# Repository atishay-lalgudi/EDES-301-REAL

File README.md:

# EDES301
Repository for EDES 301 course work

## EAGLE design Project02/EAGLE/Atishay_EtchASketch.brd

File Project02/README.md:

# EDES 301 Project 2
Digital Etch-A-Sketch PCB is a custom two-layer printed circuit board designed in Autodesk EAGLE as part of the EDES301 course. The board interfaces a NUCLEO microcontroller development board with an Adafruit SPI LCD (Model 1770 or similar), providing analog input via two potentiometers for X/Y drawing control and digital input via two push buttons for functions such as clearing the screen or mode selection. Additional features include red, green, and blue status LEDs, a MicroSD card slot for saving or loading drawings, and dedicated headers for host board connectivity. The PCB follows standard manufacturing constraints, using 10 mil signal and 15 mil power traces, 12 mil drill / 24 mil diameter vias, and Gerber RS-274X files prepared for standard CAM fabrication.

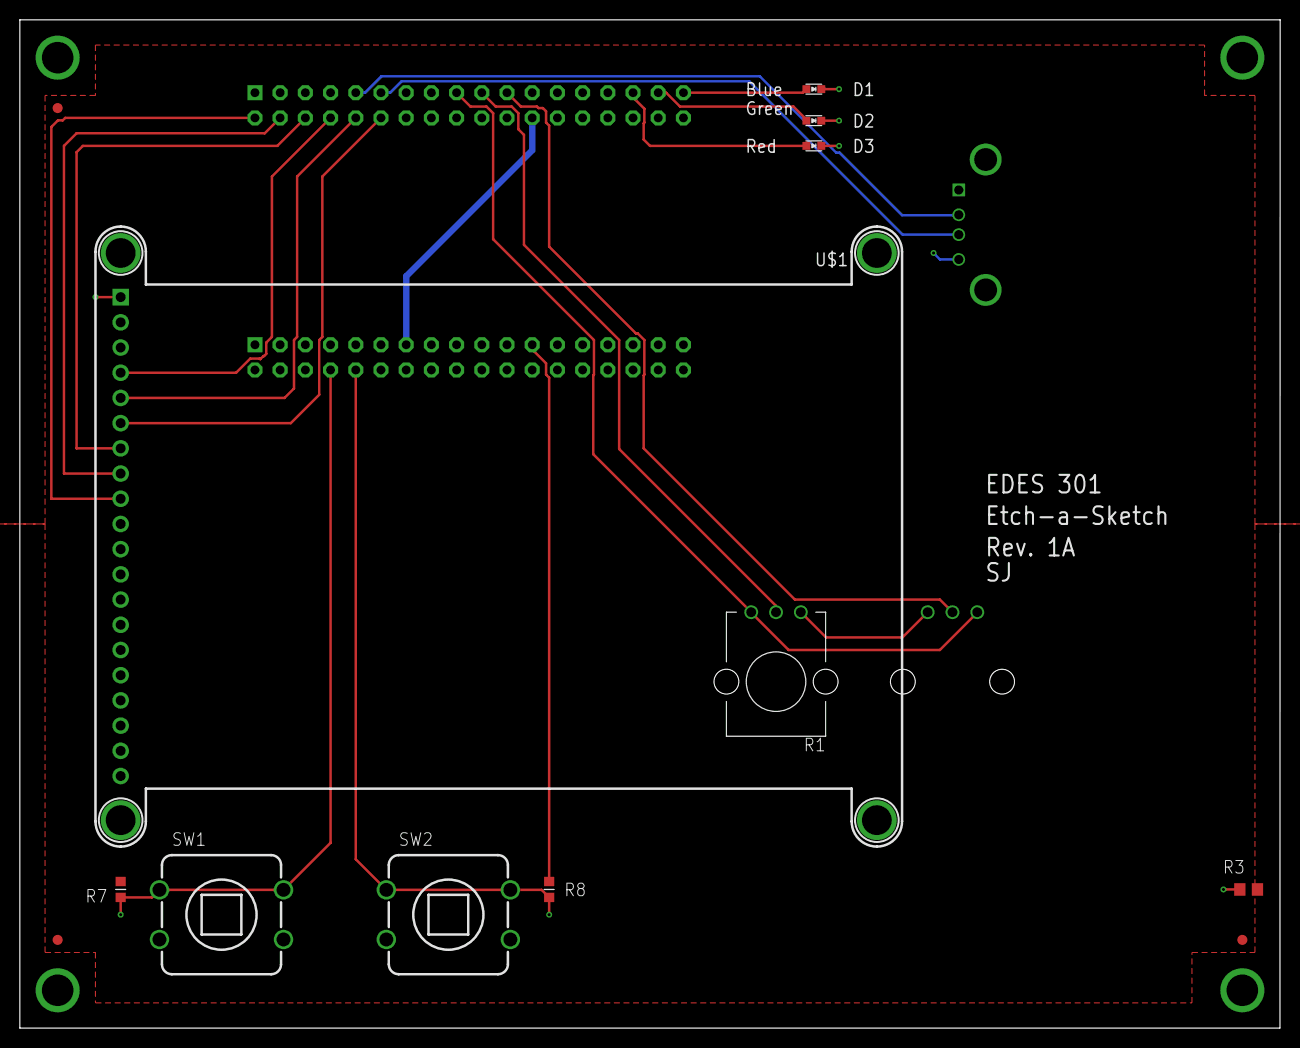
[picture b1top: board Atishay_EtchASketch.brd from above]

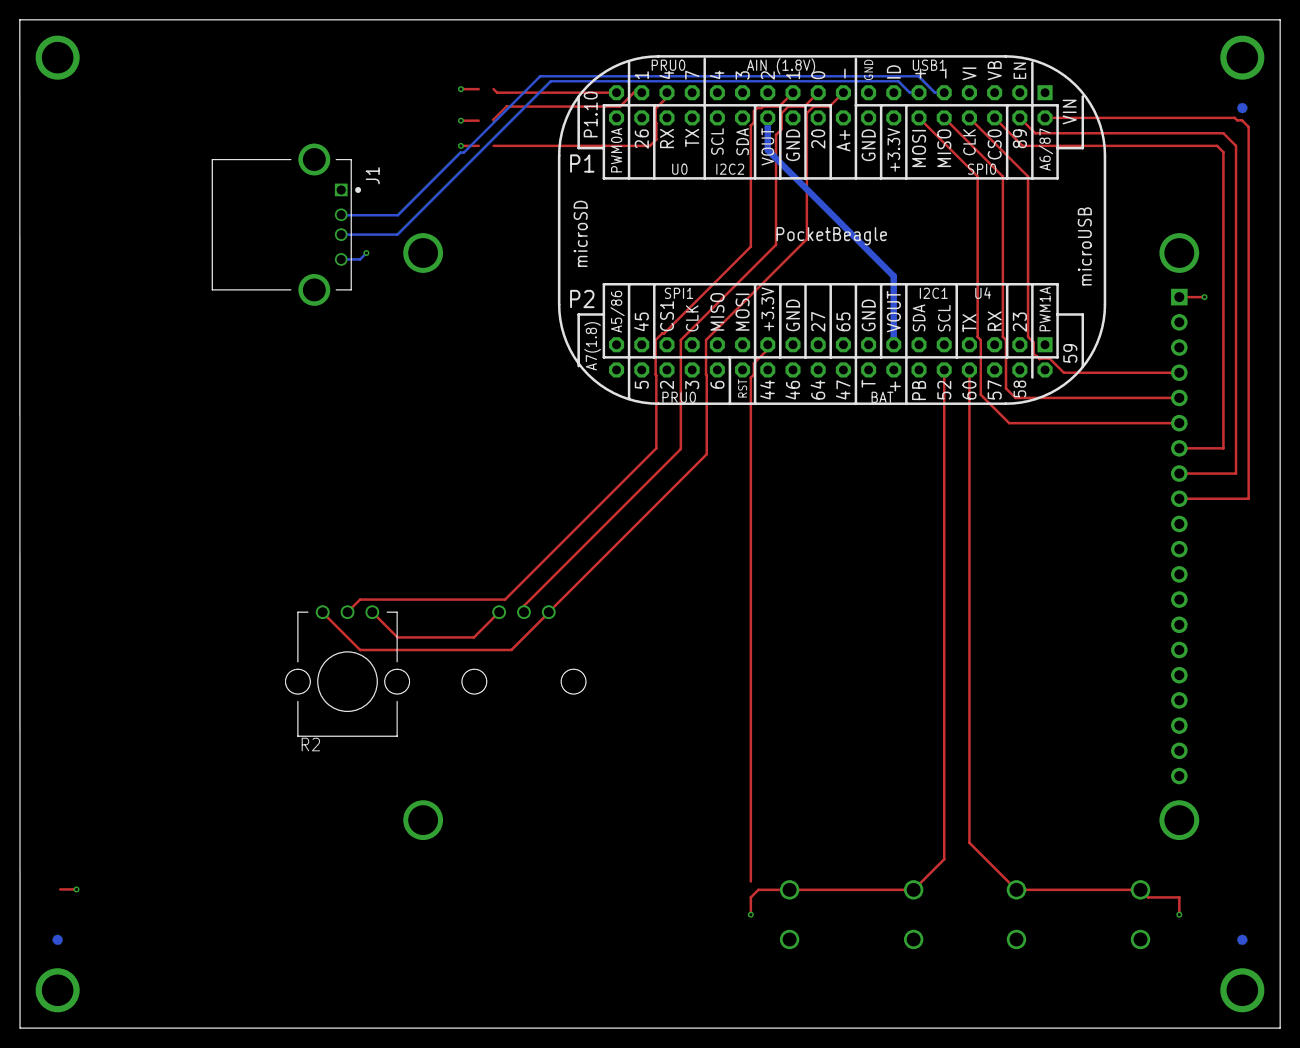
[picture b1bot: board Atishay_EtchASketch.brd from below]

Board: 4 copper layers, 127.0 x 101.6 mm, 23 parts (6 on the bottom side), 21 nets.

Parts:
D1: BLUE_LED; EIA-STD
D2: GREEN_LED; EIA-STD
D3: RED_LED; EIA-STD
FUD1, FUD2, FUD3, FUD4, FUD5, FUD6: FIDUCIAL; FIDUCIAL_40MIL
J1: 292303-1; TE_292303-1
MGT1, MGT2, MGT3, MGT4: MOUNTING_HOLE
R1: POTENTIOMETER1; POT-PO90S
R2: POTENTIOMETER2; POT-PO90S
R3: 0.1; R0805
R7, R8: 1k; R0603
SW1: PUSH_BUTTON1; BUTTON_12.5MM
SW2: PUSH_BUTTON2; BUTTON_12.5MM
U1: POCKETBEAGLE
U$1: SCREEN

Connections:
ANALOG_GND: R1.CW, R2.CW, U1.P1_17
BLUE_LED: D1.ANODE, U1.P1_35
CGND: MGT1.P$1, MGT2.P$1, MGT3.P$1, MGT4.P$1, R3.2
CLK: U1.P1_08, U$1.CLK
CS: U1.P1_06, U$1.CS
DC: U1.P1_04, U$1.DC
DN: J1.2, U1.P1_09
DP: J1.3, U1.P1_11
GND: D2.CATHODE, D3.CATHODE, J1.4, R3.1, SW1.2, SW1.4, SW2.2, SW2.4, U1.P1_15, U1.P1_16, U1.P1_22, U1.P2_15, U1.P2_21, U$1.GND
GREEN_LED: D2.ANODE, U1.P1_33
MISO: U1.P1_10, U$1.MISO
MOSI: U1.P1_12, U$1.MOSI
POTENTIOMETER1: R1.S, U1.P1_19
POTENTIOMETER2: R2.S, U1.P1_21
PUSH_BUTTON1: R7.1, SW1.1, SW1.3, U1.P2_08
PUSH_BUTTON2: R8.1, SW2.1, SW2.3, U1.P2_10
RED_LED: D3.ANODE, U1.P1_31
RST: U1.P1_02, U$1.RST
VDD_1P8V: R1.CCW, R2.CCW
VDD_3P3V: R8.2, U1.P1_14, U1.P2_23, U$1.VIN
VDD_5V: J1.1, U1.P1_24, U1.P2_13

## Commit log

2025-10-06 Create NewFolder
2025-10-06 Create empty
2025-12-04 Create NothingBurger
2025-12-04 Add files via upload
    Estimates ball X-position from time-since-velocity-reversal
    CENTER mode (X < 0.5): returns to middle | TRACK mode (X > 0.5): predicts and intercepts
    Tracks 8 Y-positions, calculates velocity from last 3 samples, predicts 10 frames ahead with bounces
    3-frame delay before direction changes prevents jitter
    0.8 zones stops micro-adjustments
    0.18 zones/frame at 20 FPS for continuity
2025-12-04 Add files via upload
    Altered from original, instantiates the connections from the PocketBeagle to the PMODs on the Basys 3, assigns those connections to up, down, and 3 bits representing the 8 zones of the ball's y-axis 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
2025-12-04 Add files via upload
    Outputs the y-axis position of the ball now
2025-12-04 Add files via upload
    Uncomments PMOD JA module, allowing connection to PocketBeagle GPIOs
    Also uncomments LEDs (not used but useful for debugging connection issues to PocketBeagle)
2025-12-16 Create ...
2025-12-20 Create GerberFiles
